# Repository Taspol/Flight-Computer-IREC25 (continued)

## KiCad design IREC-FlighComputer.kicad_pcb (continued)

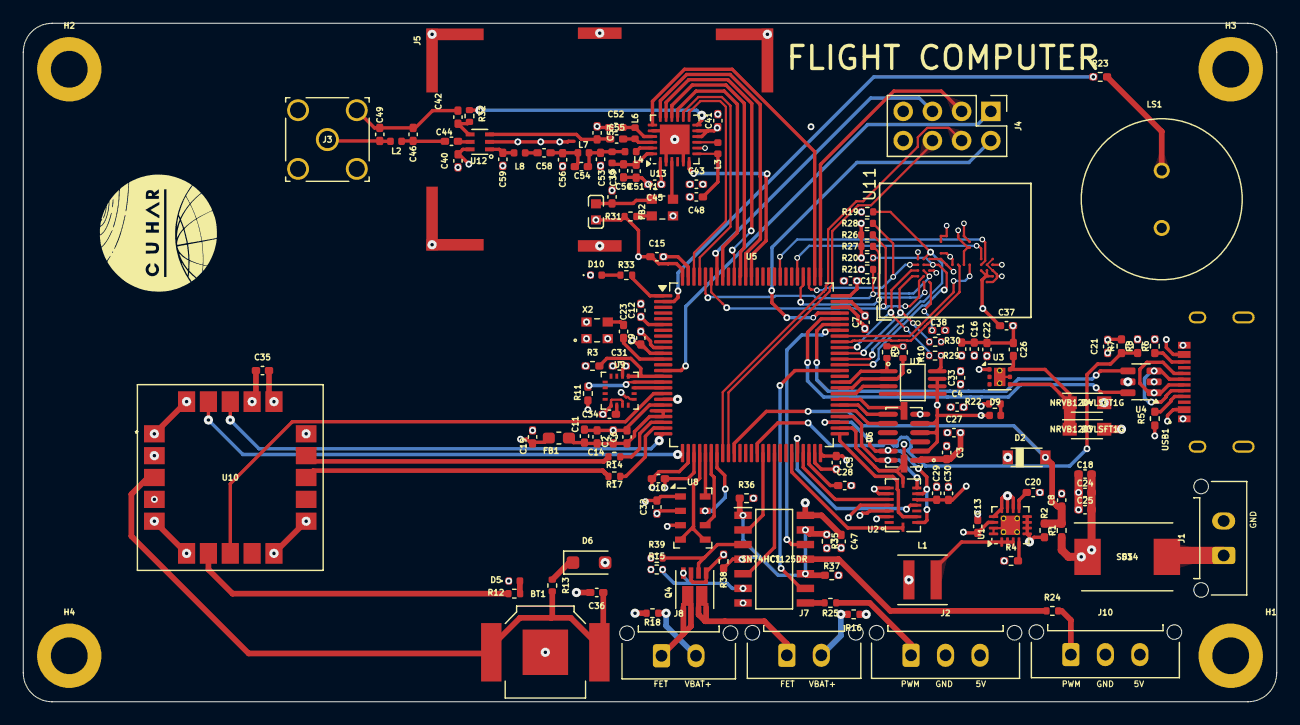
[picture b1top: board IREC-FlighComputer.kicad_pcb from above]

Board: 4 copper layers, 109.0 x 59.0 mm, 149 parts (1 on the bottom side), 120 nets.

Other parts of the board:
LOGO: LOGO
LOGO#2: LOGO

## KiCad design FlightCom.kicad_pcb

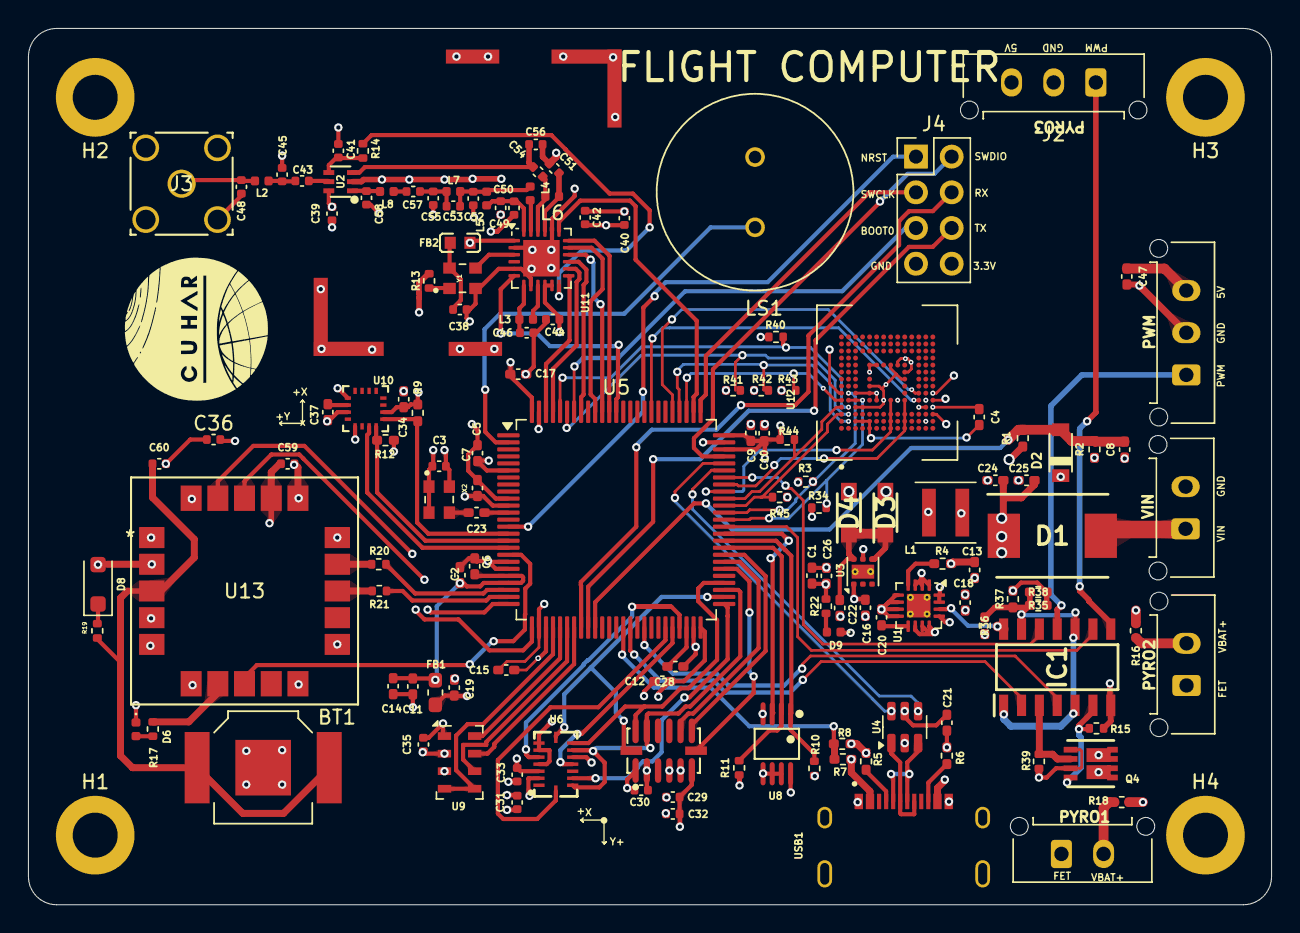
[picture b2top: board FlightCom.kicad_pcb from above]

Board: 4 copper layers, 88.4 x 62.4 mm, 144 parts (1 on the bottom side), 115 nets.

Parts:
BT1: 3098; BAT_3098
C1: 10μ; C_0402_1005Metric_Pad0.74x0.62mm_HandSolder
C2, C5, C7, C9, C10, C11, C12, C15, C17: 100n; C_0402_1005Metric_Pad0.74x0.62mm_HandSolder
C3, C30, C31, C32, C33, C35, C36, C42: 100nF; C_0402_1005Metric
C4: 0.1µF; C_0402_1005Metric_Pad0.74x0.62mm_HandSolder
C6, C14, C19: 1μ; C_0402_1005Metric_Pad0.74x0.62mm_HandSolder
C8: 100nF; C_0402_1005Metric_Pad0.74x0.62mm_HandSolder
C13: 22uF; C_0402_1005Metric_Pad0.74x0.62mm_HandSolder
C16, C22, C24, C47: 100uF; C_0402_1005Metric_Pad0.74x0.62mm_HandSolder
C18, C21, C25, C37: 10uF; C_0402_1005Metric_Pad0.74x0.62mm_HandSolder
C20: 3.3pF; C_0402_1005Metric_Pad0.74x0.62mm_HandSolder
C23: 10nF; C_0402_1005Metric_Pad0.74x0.62mm_HandSolder
C26: 2.2uF; C_0402_1005Metric_Pad0.74x0.62mm_HandSolder
C28: 4.7μ; C_0402_1005Metric_Pad0.74x0.62mm_HandSolder
C29: 10uF; C_0402_1005Metric
C34: 1uF; C_0402_1005Metric_Pad0.74x0.62mm_HandSolder
C38, C39, C44: 10nF; C_0402_1005Metric
C40: 1uF; C_0402_1005Metric
C41: 1nF; C_0402_1005Metric
C43, C57: 39pF; C_0402_1005Metric
C45, C48: 3.3pF; C_0402_1005Metric
C46: 470nF; C_0402_1005Metric
C49, C50: 47nF; C_0402_1005Metric
C51, C58: 1.8pF; C_0402_1005Metric
C52, C55: 5.6pF; C_0402_1005Metric
C53: 3.0pF; C_0402_1005Metric
C54, C56: 2.4pF; C_0402_1005Metric
C59, C60: 1.0 µF; C_0402_1005Metric
D1: SS34; DIOM7959X262N
D2: MMSZ4683T1G; SOD3716X135N
D3, D4: NRVB120VLSFT1G; SODFL3616X98N
D6, D9: LED; LED_0402_1005Metric
D8: 0.5A/40V; D_SOD-123F
FB1: 100R; L_0603_1608Metric_Pad1.05x0.95mm_HandSolder
FB2: BLM18AG601SH1D; L0603
H1, H2, H3, H4: MountingHole; MountingHole_3.2mm_M3_DIN965_Pad
IC1: SN74HCT125DR; SOIC127P600X175-14N
J1: Molex Microfit; Molex_Micro-Fit_3.0_43650-0215_1x02_P3.00mm_Vertical
J2, J10: Conn_01x03_Socket; Molex_Micro-Fit_3.0_43650-0315_1x03_P3.00mm_Vertical
J3: RF2-04A-T-00-50-G; CONN_RF2-04A-T-00-50-G_ADM
J4: Conn_02x04_Counter_Clockwise; PinHeader_2x04_P2.54mm_Vertical
J7, J8: Conn_01x02_Socket; Molex_Micro-Fit_3.0_43650-0215_1x02_P3.00mm_Vertical
J9: BMI-S-209-F; LAIRD_BMI-S-209-F
L1: 2.2uH; L_Coilcraft_XxL4020
L2: 9.1nH; L_0402_1005Metric
L3, L6: 15nH; L_0402_1005Metric
L4: 0R; L_0402_1005Metric
L5: 47nH; L_0402_1005Metric
L7: 2.5nH; L_0402_1005Metric
L8: 4.7nH; L_0402_1005Metric
LOGO: LOGO
LOGO#2: LOGO
LS1: PS1440P02BT; BUZZER_PS1440P02BT
Q4: SI7232DN-T1-GE3; TRANS_SI7232DN-T1-GE3
R1, R7: 10k; R_0402_1005Metric_Pad0.72x0.64mm_HandSolder
R2: 47k; R_0402_1005Metric_Pad0.72x0.64mm_HandSolder
R3, R34, R40, R41, R42, R43, R44, R45: 10K; R_0402_1005Metric
R4: 100k; R_0402_1005Metric_Pad0.72x0.64mm_HandSolder
R5, R6: 5.1k; R_0402_1005Metric_Pad0.72x0.64mm_HandSolder
R8: 22k; R_0402_1005Metric_Pad0.72x0.64mm_HandSolder
R9, R12: 2.7k; R_0402_1005Metric_Pad0.72x0.64mm_HandSolder
R10, R11: 2.7k; R_0402_1005Metric
R13: 10k; R_0402_1005Metric
R14: 100; R_0402_1005Metric
R15, R39: 3.3K; R_0402_1005Metric
R16, R18: 5R; R_0402_1005Metric
R17, R22: 1k; R_0402_1005Metric
R19: 3.3k; R_0402_1005Metric
R20, R21: 470; R_0402_1005Metric
R35, R36, R37, R38: 470R; R_0402_1005Metric_Pad0.72x0.64mm_HandSolder
U1: TPS62153; VQFN-16-1EP_3x3mm_P0.5mm_EP1.68x1.68mm_ThermalVias
U2: PE4259-63; SC-70-6_L2.2-W1.3-P0.65-LS2.1-BL
U3: LP5912Q3.3DRVRQ1; WSON-6-1EP_2x2mm_P0.65mm_EP1x1.6mm_ThermalVias
U4: USBLC6-2SC6; SOT-23-6
U5: STM32U575VGTx; LQFP-100_14x14mm_P0.5mm
U6: BMI088; LGA-16_L4.5-W3.0-P0.50-BL
U7: ADXL375BCCZ-RL7; LGA-14_L5.0-W3.0-P0.80-BL
U8: TMP275AIDGKR VSSOP8; VSSOP-8_L3.0-W3.0-P0.65-LS5.0-BL
U9: MS5607-02BA; LGA-8_3x5mm_P1.25mm
U10: MMC5983MA; LGA-16_L3.0-W3.0-P0.50-BL_SQ
U11: SX1262IMLTRT; QFN-24-1EP_4x4mm_P0.5mm_EP2.6x2.6mm
U12: THGBMNG5D1LBAIT; BGA153N50P14X14_1000X1100X80
U13: SAM-M10Q-00B; SAM-M10Q_UBL
USB1: 10172013-00011LF; AMPHENOL_10172013-00011LF
X2: ECS-TXO-32CSMV-320-AN-TR; OSC_ECS-TXO-2520-33-320-AN-TR
Y1: 32 MHz TCXO; OSC_ECS-TXO-2520-33-320-AN-TR

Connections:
+3.3V: C1.1, C3.1, C5.1, C7.1, C9.1, C10.1, C12.1, C15.1, C16.2, C17.2, C19.1, C26.2, C29.2, C30.1, C31.1, C32.2, C33.1, C34.2, C35.2, C36.2, C39.2, C40.1, C42.1, C44.1, C59.1, D8.2 (A), FB1.1, FB2.2, J4.8, R3.1, R9.1, R10.1, R11.1, R12.2, R13.1, R22.1, R34.1, R40.1, R41.1, R42.1, R43.1, R44.1, R45.1, U2.6 (CTRL#orVDD), U3.1 (OUT), U5.6 (VBAT), U5.11 (VDD), U5.28 (VDD), U5.50 (VDD), U5.73 (VDDUSB), U5.75 (VDD), U5.100 (VDD), U6.3 (VDD), U6.11 (VDDIO), U7.1 (VDDI/O), U7.6 (VS), U8.8 (V+), U9.1 (VDD), U10.2 (VDD), U10.13 (VDDIO), U11.1 (VDD_IN), U11.10 (VBAT), U11.11 (VBAT_IO), U12.C6 (VCCQ), U12.E6 (VCC), U12.E9 (VSF), U12.E10 (VSF__1), U12.F5 (VCC__1), U12.F10 (VSF__2), U12.J10 (VCC__2), U12.K9 (VCC__3), U12.M4 (VCCQ__1), U12.N4 (VCCQ__2), U12.P3 (VCCQ__3), U12.P5 (VCCQ__4), U13.2 (V_IO), U13.17 (VCC), X2.4 (VDD)
+5V: C13.2, C47.1, D3.2 (A), IC1.14 (VCC), J2.3, J10.3, L1.1, R4.1, U1.14 (VOS)
/PWM_PD: IC1.1 (1~OE), IC1.5 (2A), IC1.10 (3~OE), IC1.13 (4~OE), R35.1, R36.1, R37.1, R38.1
ADXL375_CS: U5.56 (PD9), U7.7 (~CS)
ADXL375_INT1: U5.58 (PD11), U7.8 (INT1)
ADXL375_INT2: U5.57 (PD10), U7.9 (INT2)
ADXL375_SCLK: U5.52 (PB13), U6.8 (SCL/SCK), U7.14 (SCL/SCLK)
ADXL375_SDI: U5.54 (PB15), U6.9 (SDA/SDI), U7.13 (SDA/SDI/SDIO)
ADXL375_SDO: U5.53 (PB14), U6.10 (SDO2), U6.15 (SDO1), U7.12 (SDO/ALTADDRESS)
ANT_SW: R14.1, U11.12 (DIO2)
BAT_LEVEL: C8.2, D2.A, R1.2, R2.1, U5.35 (PB0)
BCD: R7.2, R8.1, U5.39 (PE8)
BMI088_ACCEL_CS: U5.51 (PB12), U6.14 (CSB1)
BMI088_ACCEL_INT: U5.45 (PE14), U6.16 (INT1)
BMI088_GYRO_CS: U5.47 (PB10), U6.5 (CSB2)
BMI088_GYRO_INT: U5.46 (PE15), U6.12 (INT3)
BOOT0: J4.5, U5.94 (PH3)
Backup: BT1.P1, BT1.P2, C60.1, R19.2, U13.3 (V_BCKP)
COMPANION_RX: J4.4, U5.33 (PC4)
COMPANION_TX: J4.6, U5.34 (PC5)
D+: U4.1 (I/O1), USB1.A6 (DP1), USB1.B6 (DP2)
D-: U4.3 (I/O2), USB1.A7 (DN1), USB1.B7 (DN2)
EMMC_CLK: U5.80 (PC12), U12.M6 (CLK)
EMMC_CMD: U5.83 (PD2), U12.M5 (CMD)
EMMC_DAT0: R45.2, U5.65 (PC8), U12.A3 (DAT0)
EMMC_DAT1: R44.2, U5.66 (PC9), U12.A4 (DAT1)
EMMC_DAT2: R43.2, U5.78 (PC10), U12.A5 (DAT2)
EMMC_DAT3: R42.2, U5.79 (PC11), U12.B2 (DAT3)
EMMC_DAT4: R41.2, U5.95 (PB8), U12.B3 (DAT4)
EMMC_DAT5: R40.2, U5.96 (PB9), U12.B4 (DAT5)
EMMC_DAT6: R34.2, U5.63 (PC6), U12.B5 (DAT6), U12.C5 (NC__20)
EMMC_DAT7: R3.2, U5.64 (PC7), U12.B6 (DAT7)
EMMC_DATASTROBE: U5.67 (PA8), U12.H1 (NC__53), U12.H2 (NC__54), U12.H3 (NC__55), U12.H5 (DS)
EMMC_RSTN: U5.68 (PA9), U12.K1 (NC__65), U12.K2 (NC__66), U12.K3 (NC__67), U12.K5 (~RST)
GNSS_INT: U5.26 (PA3), U13.19 (EXTINT)
GNSS_RX: R20.1, U5.23 (PA0)
GNSS_Reset: U5.25 (PA2), U13.18 (RESET_N)
GNSS_SafeBoot: U5.18 (PC3), U13.8 (SAFEBOOT_N)
GNSS_TX: R21.1, U5.24 (PA1)
HSE_IN: C23.1, U5.12 (PH0)
MMC5983MA_INT: U5.17 (PC2), U10.15 (INT)
MMC5983MA_SCL: R9.2, U5.15 (PC0), U10.1 (SCL/SPI_SCK)
MMC5983MA_SDA: R12.1, U5.16 (PC1), U10.16 (SDA/SPI_SDI)
MS5607_MISO: U5.31 (PA6), U9.6 (SDO)
MS5607_MOSI: U5.32 (PA7), U9.7 (SDI/SDA)
MS5607_NSS: U5.29 (PA4), U9.4 (CSB), U9.5 (CSB)
MS5607_SCLK: U5.30 (PA5), U9.8 (SCLK)
unnamed: C43.1, C45.2, L2.1
unnamed: C48.2, J3.1, L2.2
unnamed: C52.1, C53.1, L4.2, L5.1, L7.1
unnamed: C53.2, C55.1, C57.1, L7.2
unnamed: C57.2, L8.1
unnamed: D1.2 (A), J1.1
unnamed: C22.1, D3.1 (K), D4.1 (K), U3.4 (EN), U3.6 (IN)
unnamed: D6.2 (A), R17.2
unnamed: D8.1 (K), R19.1
unnamed: D9.2 (A), R22.2
unnamed: J7.1, Q4.7, Q4.8, Q4.9
unnamed: J7.2, R16.2
unnamed: J8.1, Q4.5, Q4.6, Q4.10
unnamed: J8.2, R18.2
unnamed: L1.2, U1.1 (SW), U1.2 (SW), U1.3 (SW)
unnamed: R4.2, U1.4 (PG)
unnamed: C20.2, U1.9 (SS/TR)
unnamed: C41.2, R14.2, U2.4 (CTRL)
unnamed: C43.2, U2.5 (RFC)
unnamed: C28.1, U5.48 (VCAP)
unnamed: C37.1, U10.10 (CAP)
unnamed: L3.2, U11.9 (DCC_SW)
unnamed: C54.1, L6.2, U11.22 (RFI_N)
unnamed: C51.2, L6.1, U11.21 (RFI_P)
unnamed: L4.1, U11.23 (RFO)
unnamed: C46.1, L3.1, U11.7 (VREG)
unnamed: C49.1, C50.1, L5.2, U11.24 (VR_PA)
unnamed: C4.2, U12.C2 (VDDI), U12.D2 (NC__30), U12.E1 (NC__36), U12.E2 (NC__37)
unnamed: R20.2, U13.14 (RXD)
unnamed: R21.2, U13.13 (TXD)
unnamed: R5.2, USB1.A5 (CC1)
unnamed: R6.1, USB1.B5 (CC2)
unnamed: C23.2, X2.3 (OUTPUT)
unnamed: R13.2, Y1.1 (TRI-STATE)
unnamed: C38.1, FB2.1, Y1.4 (VDD)
PPS: R17.1, U13.7 (TIMEPULSE)
PWM_A: IC1.2 (1A), U5.40 (PE9)
PWM_B: IC1.4 (2~OE), U5.42 (PE11)
PWM_Buzzer: LS1.1, U5.2 (PE3)
PWM_C: IC1.9 (3A), U5.62 (PD15)
PWM_D: IC1.12 (4A), U5.69 (PA10)
PYRO_A: IC1.3 (1Y), Q4.2, R39.2
PYRO_B: IC1.6 (2Y), Q4.4, R15.2
PYRO_C: IC1.8 (3Y), J2.1
RF1: C58.2, L8.2, U2.1 (RF1)
RF2: C54.2, C56.2, U2.3 (RF2)
SERVO_A: IC1.11 (4Y), J10.1
SWCLK: J4.3, U5.76 (PA14)
SWDIO: J4.2, U5.72 (PA13)
SX1262_BUSY: U5.97 (PE0), U11.14 (BUSY)
SX1262_DIO1: U5.98 (PE1), U11.13 (DIO1)
SX1262_DIO3: U5.88 (PD7), U11.6 (DIO3)
SX1262_MISO: U5.90 (PB4), U11.16 (MISO)
SX1262_MOSI: U5.91 (PB5), U11.17 (MOSI)
SX1262_NSS: U5.77 (PA15), U11.19 (NSS)
SX1262_RST: U5.93 (PB7), U11.15 (~RESET)
SX1262_SCK: U5.89 (PB3), U11.18 (SCK)
TMP275_ALERT: U5.61 (PD14), U8.3 (ALERT)
TMP275_SCL: R11.2, U5.59 (PD12), U8.2 (SCL)
TMP275_SDA: R10.2, U5.60 (PD13), U8.1 (SDA)
USB_DN: U4.4 (I/O2), U5.70 (PA11)
USB_DP: U4.6 (I/O1), U5.71 (PA12)
VBAT+: C18.2, C24.2, C25.2, D1.1 (K), R1.1, R16.1, R18.1, U1.10 (VIN), U1.11 (VIN), U1.12 (VIN), U1.13 (EN)
VBAT-: BT1.N, C1.2, C2.2, C3.2, C4.1, C5.2, C6.2, C7.2, C8.1, C9.2, C10.2, C11.2, C12.2, C13.1, C14.2, C15.2, C16.1, C17.1, C18.1, C19.2, C20.1, C21.1, C22.2, C24.1, C25.1, C26.1, C28.2, C29.1, C30.2, C31.2, C32.1, C33.2, C34.1, C35.1, C36.1, C37.2, C38.2, C39.1, C40.2, C41.1, C42.2, C44.2, C45.1, C46.2, C47.2, C48.1, C49.2, C50.2, C51.1, C52.2, C55.2, C56.1, C58.1, C59.2, C60.2, D2.C, D6.1 (K), D9.1 (K), IC1.7 (GND), J1.2, J2.2, J3.2, J3.3, J3.4, J3.5, J4.7, J9.S3 (SHIELD), J9.S6 (SHIELD), J9.S9 (SHIELD), J9.S10 (SHIELD), J10.2, LS1.2, Q4.1, Q4.3, R2.2, R5.1, R6.2, R8.2, R15.1, R35.2, R36.2, R37.2, R38.2, R39.1, U1.5 (FB), U1.6 (GND), U1.7 (FSW), U1.8 (DEF), U1.15 (GND), U1.16 (GND), U1.17 (GND), U2.2 (GND), U3.5 (GND), U3.7 (EP), U4.2 (GND), U5.10 (VSS), U5.19 (VSSA), U5.20 (VREF-), U5.27 (VSS), U5.49 (VSS), U5.74 (VSS), U5.99 (VSS), U6.2 (NC), U6.4 (GNDA), U6.6 (GNDIO), U6.7 (PS), U7.2 (GND), U7.4 (GND), U7.5 (GND), U8.4 (GND), U8.5 (A2), U8.6 (A1), U8.7 (A0), U9.2 (PS), U9.3 (GND), U10.9 (GND), U10.11 (GND), U11.2 (GND), U11.5 (GND), U11.8 (GND), U11.20 (GND), U11.25 (GND), U12.A6 (VSS), U12.C4 (VSSQ), U12.D4 (NC__32), U12.E7 (VSS__1), U12.G5 (VSS__2), U12.H10 (VSS__3), U12.J5 (VSS__4), U12.K8 (VSS__5), U12.N2 (VSSQ__1), U12.N5 (VSSQ__2), U12.P4 (VSSQ__3), U12.P6 (VSSQ__4), U13.1 (GND), U13.4 (GND), U13.5 (GND), U13.6 (GND), U13.10 (GND), U13.11 (GND), U13.15 (GND), U13.16 (GND), U13.20 (GND), USB1.1 (MH1), USB1.2 (MH2), USB1.3 (MH3), USB1.4 (MH4), USB1.A1 (GND_1), USB1.A12 (GND_2), X2.1 (GROUND_1), X2.2 (GROUND_2), Y1.2 (GND)
VBUS: C21.2, D4.2 (A), R7.1, U4.5 (VBUS), USB1.A4 (VBUS_1), USB1.A9 (VBUS_2)
VREF+: C2.1, C6.1, C11.1, C14.1, FB1.2, U5.21 (VREF+), U5.22 (VDDA)
XTA: U11.3 (XTA), Y1.3 (OUTPUT)
nRST: J4.1, U5.14 (NRST)

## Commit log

2025-03-02 first push
2025-03-02 reassign pin
2025-03-02 asdf
2025-03-02 Arranged pin
2025-03-02 reArrange pins
2025-03-02 add power LED
2025-03-02 update label
2025-03-16 add EMMC
2025-03-16 update schematic
2025-03-16 update footprint
2025-03-16 routing
2025-03-23 reroute
2025-03-23 rm led
2025-03-23 run checked
2025-03-23 rearrange
2025-03-24 cleanup track and vias
2025-03-24 run drc
2025-03-24 drc checked
2025-03-24 changed logo
2025-03-24 adjust via size
2025-03-24 update connection
2025-03-24 add buzzer
2025-03-24 adjust position
2025-03-25 improve routing
2025-03-29 improve
2025-03-29 improved
2025-04-01 for frab
2025-04-14 updated schematic
2025-04-18 new layout
2025-04-20 update layout
2025-04-20 add gerber file
2025-04-20 rm used file
2025-04-20 rm unused file
2025-04-20 add silk screen
